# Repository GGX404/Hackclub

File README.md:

# Chase's Better Stream Deck
The BSD is a multifunctional Macropad designed to be a low cost, high function replacement to the expensive macropads currently found on the market.

## 3D Model

My model has 3 main parts:

- Top Cover to hide PCB
  
- Main Case (at 20 degree incline for eaiser reachability)
  
- PCB

Above are the parts from left to right.
## PCB
PCB Made in KiCad

Schematic:

PCB:

## Firmware

Uses KMK for firmware. Macros are handled by AutoHotKey.

## BOM

Materials Required:
- 1 Seeed XIAO RP2040
  
- 9 MX-Style switches

- 9 Through-hole 1N4148 Diodes

- 9 Keycaps (I would 3d print your own so you can add your own logos onto them)

- 4 M3x16mm screws

- 4 M3x5mx4mm heatset inserts

- 1 Case (2 3D printed parts)

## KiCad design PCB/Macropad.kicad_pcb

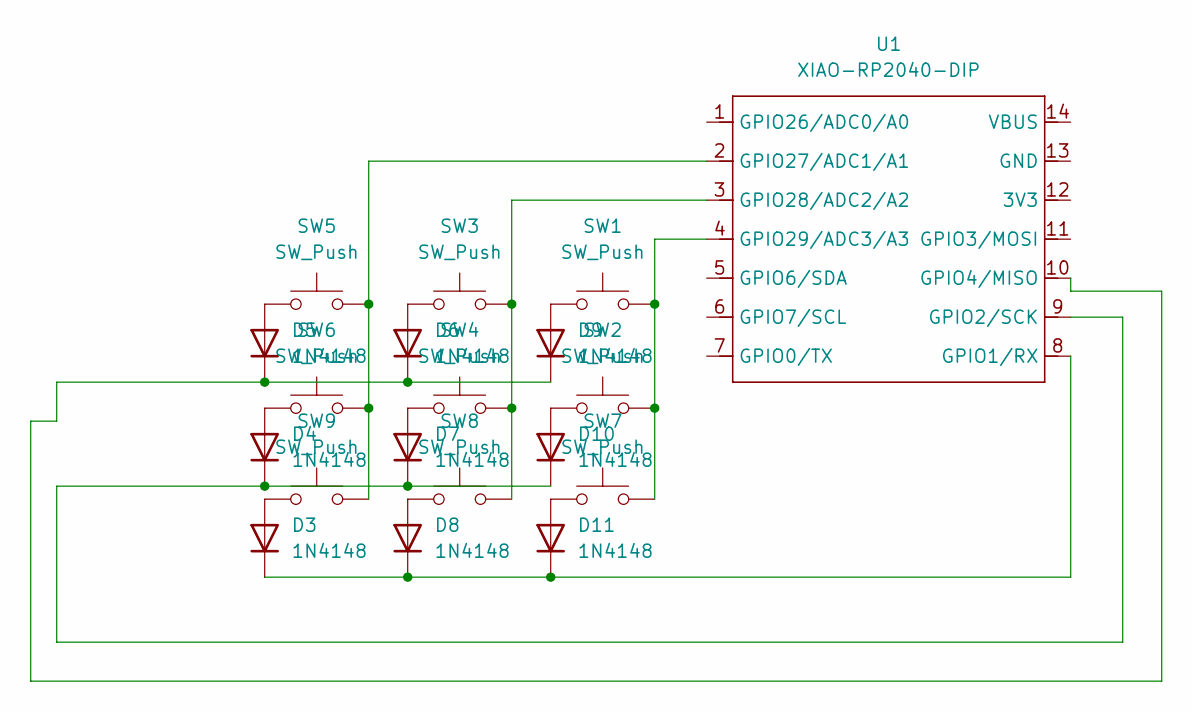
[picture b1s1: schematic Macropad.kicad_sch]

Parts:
D3, D4, D5, D6, D7, D8, D9, D10, D11: 1N4148; D_DO-35_SOD27_P7.62mm_Horizontal
SW1, SW2, SW3, SW4, SW5, SW6, SW7, SW8, SW9: SW_Push; SW_Cherry_MX_1.00u_PCB
U1: XIAO-RP2040-DIP

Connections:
unnamed: D3.2 (A), SW9.1
unnamed: D4.2 (A), SW6.1
unnamed: D5.2 (A), SW5.1
unnamed: D5.1 (K), D6.1 (K), D9.1 (K), U1.10 (GPIO4/MISO)
unnamed: D6.2 (A), SW3.1
unnamed: D7.2 (A), SW4.1
unnamed: D8.2 (A), SW8.1
unnamed: D9.2 (A), SW1.1
unnamed: D10.2 (A), SW2.1
unnamed: D4.1 (K), D7.1 (K), D10.1 (K), U1.9 (GPIO2/SCK)
unnamed: D11.2 (A), SW7.1
unnamed: D3.1 (K), D8.1 (K), D11.1 (K), U1.8 (GPIO1/RX)
unnamed: SW5.2, SW6.2, SW9.2, U1.2 (GPIO27/ADC1/A1)
unnamed: SW3.2, SW4.2, SW8.2, U1.3 (GPIO28/ADC2/A2)
unnamed: SW1.2, SW2.2, SW7.2, U1.4 (GPIO29/ADC3/A3)

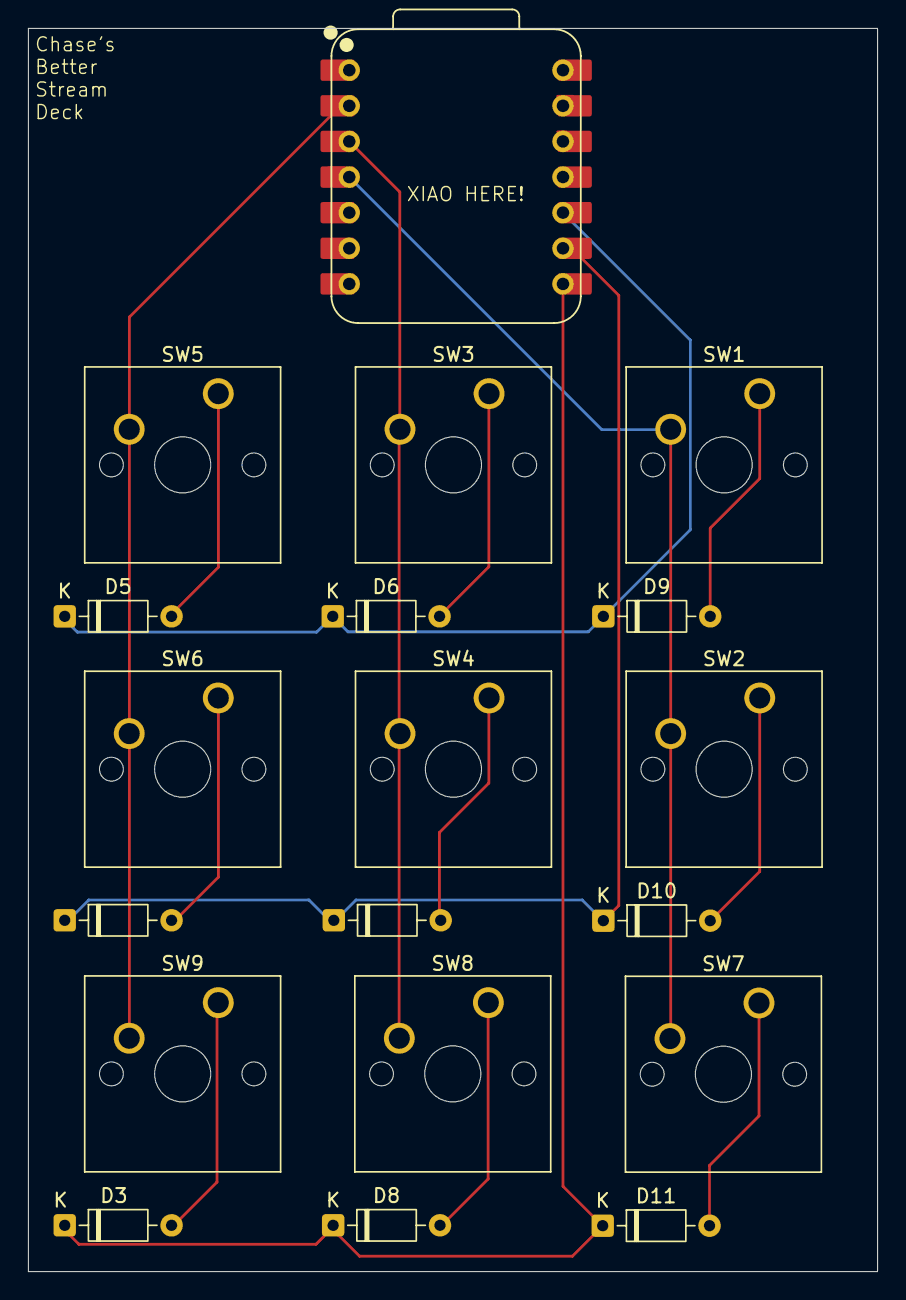
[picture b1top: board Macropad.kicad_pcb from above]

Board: 2 copper layers, 60.5 x 88.7 mm, 19 parts (0 on the bottom side), 15 nets.

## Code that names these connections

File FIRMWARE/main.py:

import board
from kmk.kmk_keyboard import KMKKeyboard
from kmk.keys import KC
from kmk.scanners import DiodeOrientation
from kmk.modules.macros import Macros
from kmk.extensions.media_keys import MediaKeys

keyboard = KMKKeyboard()
macros = Macros()
keyboard.modules.append(macros)
keyboard.extensions.append(MediaKeys())
keyboard.col_pins = (board.GPIO27, board.GPIO28, board.GPIO29)
keyboard.row_pins = (board.GPIO4, board.GPIO2, board.GPIO1)
keyboard.diode_orientation = DiodeOrientation.COL2ROW

# The macros look strange because i am using autohotkey to quickly launch them for me.
OPEN_DISCORD = KC.MACRO(KC.LCTL(KC.LALT(KC.LSFT(KC.F1))))
OPEN_STEAM   = KC.MACRO(KC.LCTL(KC.LALT(KC.LSFT(KC.F2))))
OPEN_LOGITECH = KC.MACRO(KC.LCTL(KC.LALT(KC.LSFT(KC.F3))))

rows = [
    [OPEN_DISCORD,       OPEN_STEAM,         OPEN_LOGITECH],
    [KC.AUDIO_VOL_UP,    KC.AUDIO_VOL_DOWN,  KC.AUDIO_MUTE],
    [KC.MEDIA_PREV_TRACK, KC.MEDIA_STOP,      KC.MEDIA_NEXT_TRACK]
]

keyboard.keymap = [rows]

if __name__ == '__main__':
    keyboard.go()

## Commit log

2025-12-28 Add firmware and folders
2025-12-28 Added CAD and PCB
2025-12-28 Added Pictures
2025-12-28 Fixed spelling problem
2025-12-28 Added README
2025-12-28 Added Revisions
2025-12-28 redone README
